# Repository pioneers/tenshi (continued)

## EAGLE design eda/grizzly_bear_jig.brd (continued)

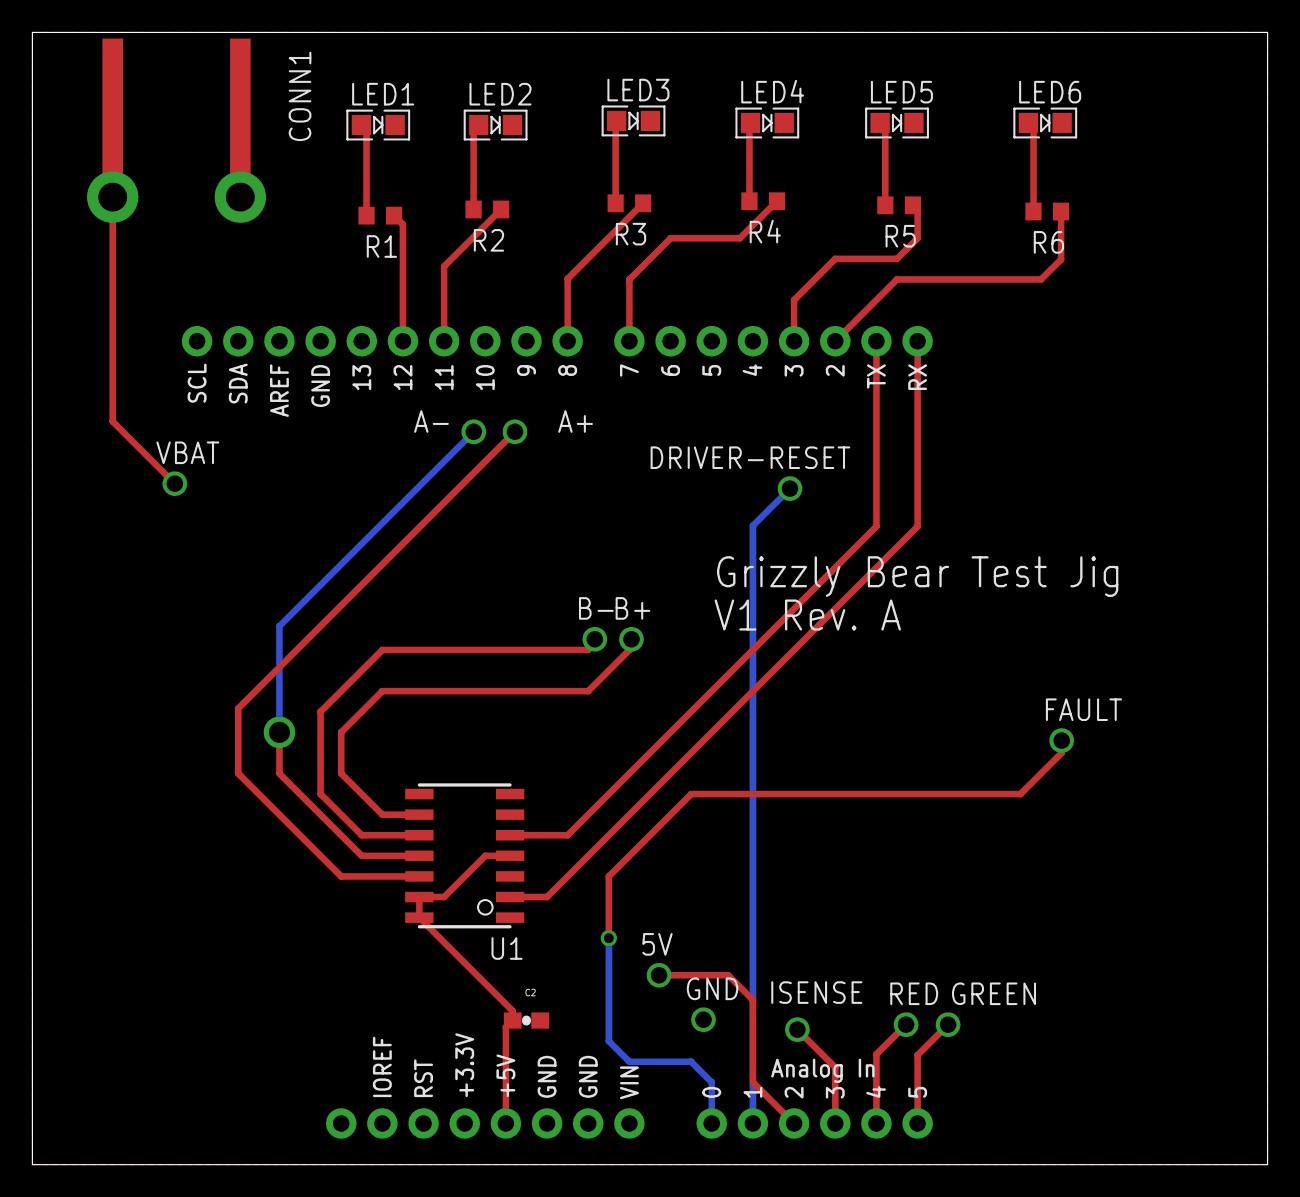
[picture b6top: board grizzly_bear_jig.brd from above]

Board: 2 copper layers, 76.2 x 69.8 mm, 28 parts (0 on the bottom side), 27 nets.

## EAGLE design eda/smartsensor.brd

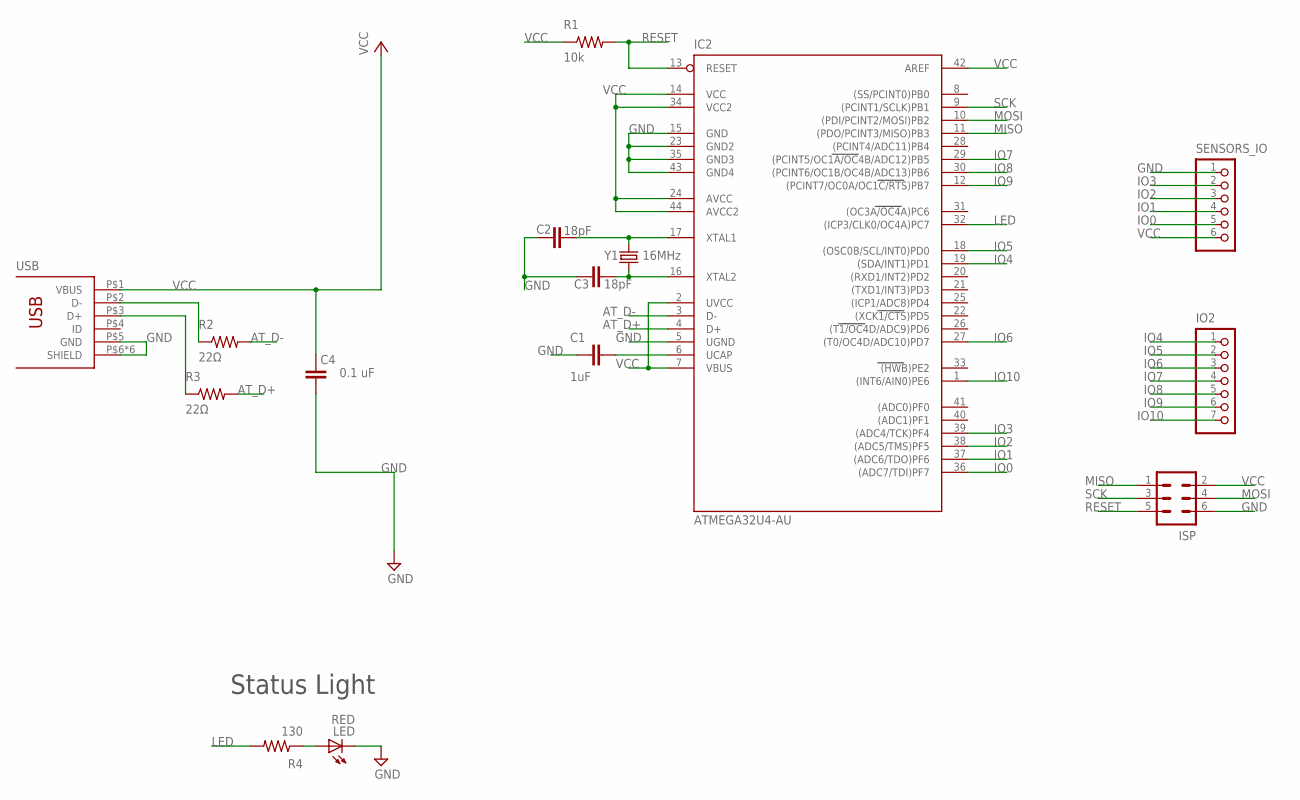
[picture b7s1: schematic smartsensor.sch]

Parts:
C1: 1uF; 0603-CAP
C2, C3: 18pF; 0603-CAP
C4: 0.1 uF; 0603-CAP
IC2: ATMEGA32U4-AU; TQFP44
IO2: PINHD-1X7; 1X07
ISP: MA03-2
LED: RED; LED-0805
R1: 10k; R0603
R2, R3: 22Ω; R0603
R4: 130; R0603
SENSORS_IO: PINHD-1X6STRAIN-RELIEF; 1X06-STRAINRELIEF
USB: USB-OTGMICRO-AB; USB-MICRO-AB
Y1: 16MHz; CRYSTAL-SMD-5.0X3.2-2PIN

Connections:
AT_D+: IC2.4 (D+), R3.2
AT_D-: IC2.3 (D-), R2.2
GND: C1.1, C2.1, C3.1, C4.1, IC2.5 (UGND), IC2.15 (GND), IC2.23 (GND2), IC2.35 (GND3), IC2.43 (GND4), ISP.6, LED.C, SENSORS_IO.1, USB.P$5 (GND), USB.P$6 (SHIELD), USB.P$7 (SHIELD), USB.P$8 (SHIELD), USB.P$9 (SHIELD), USB.P$10 (SHIELD), USB.P$11 (SHIELD)
IO0: IC2.36 ((ADC7/TDI)PF7), SENSORS_IO.5
IO1: IC2.37 ((ADC6/TDO)PF6), SENSORS_IO.4
IO2: IC2.38 ((ADC5/TMS)PF5), SENSORS_IO.3
IO3: IC2.39 ((ADC4/TCK)PF4), SENSORS_IO.2
IO4: IC2.19 ((SDA/INT1)PD1), IO2.1
IO5: IC2.18 ((OSC0B/SCL/INT0)PD0), IO2.2
IO6: IC2.27 ((T0/OC4D/ADC10)PD7), IO2.3
IO7: IC2.29 ((PCINT5/OC1A/OC4B/ADC12)PB5), IO2.4
IO8: IC2.30 ((PCINT6/OC1B/OC4B/ADC13)PB6), IO2.5
IO9: IC2.12 ((PCINT7/OC0A/OC1C/RTS)PB7), IO2.6
IO10: IC2.1 ((INT6/AIN0)PE6), IO2.7
LED: IC2.32 ((ICP3/CLK0/OC4A)PC7), R4.2
MISO: IC2.11 ((PDO/PCINT3/MISO)PB3), ISP.1
MOSI: IC2.10 ((PDI/PCINT2/MOSI)PB2), ISP.4
unnamed: C1.2, IC2.6 (UCAP)
unnamed: R3.1, USB.P$3 (D+)
unnamed: R2.1, USB.P$2 (D-)
unnamed: C2.2, IC2.17 (XTAL1), Y1.P$2 (2)
unnamed: C3.2, IC2.16 (XTAL2), Y1.P$1 (1)
unnamed: LED.A, R4.1
RESET: IC2.13 (RESET), ISP.5, R1.2
SCK: IC2.9 ((PCINT1/SCLK)PB1), ISP.3
VCC: C4.2, IC2.2 (UVCC), IC2.7 (VBUS), IC2.14 (VCC), IC2.24 (AVCC), IC2.34 (VCC2), IC2.42 (AREF), IC2.44 (AVCC2), ISP.2, R1.1, SENSORS_IO.6, USB.P$1 (VBUS)

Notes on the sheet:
Status Light

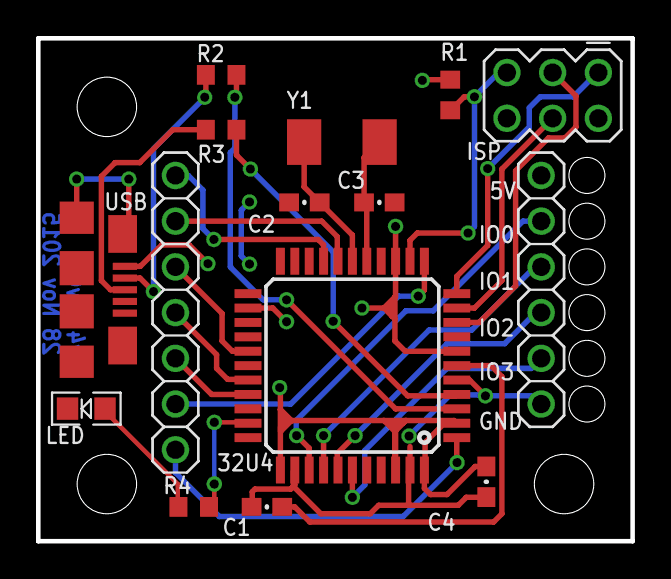
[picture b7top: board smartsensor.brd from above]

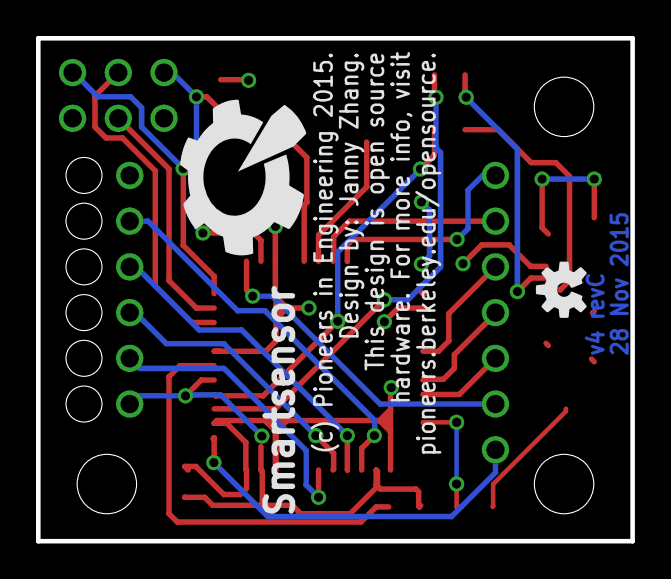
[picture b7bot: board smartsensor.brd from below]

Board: 2 copper layers, 33.0 x 27.9 mm, 20 parts (2 on the bottom side), 26 nets.

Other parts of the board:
HOLE1, HOLE2, HOLE3: STAND-OFF
U$1: PIE-LOGO-SMALL
U$2: OSHW-LOGO-S

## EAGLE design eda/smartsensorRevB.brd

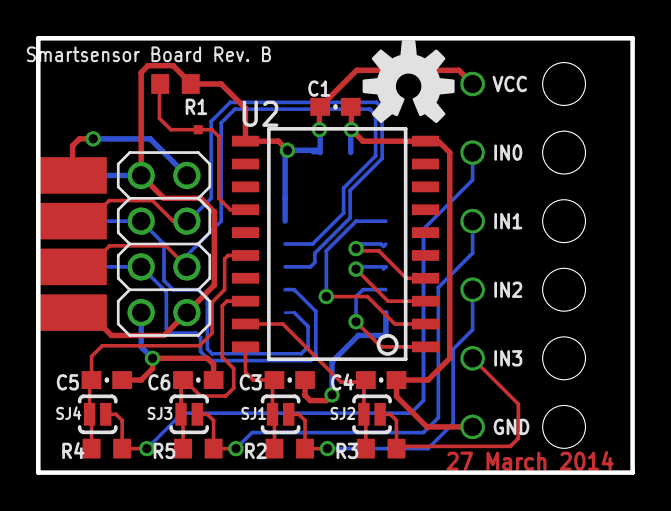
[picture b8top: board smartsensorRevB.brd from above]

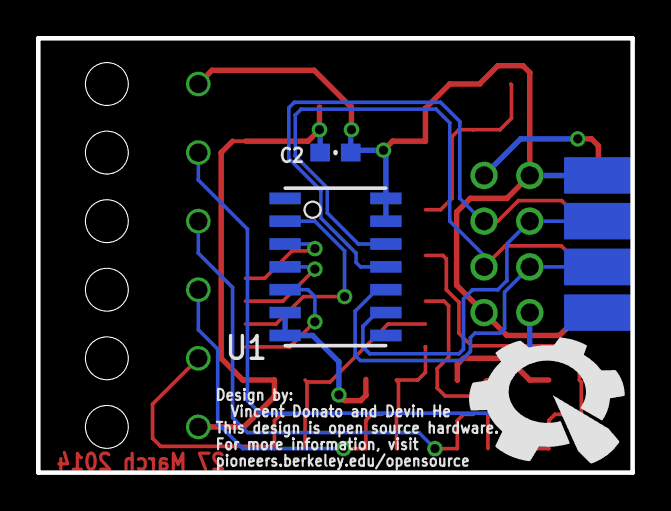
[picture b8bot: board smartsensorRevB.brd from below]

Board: 2 copper layers, 33.0 x 24.1 mm, 28 parts (3 on the bottom side), 19 nets.

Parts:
C1, C2: 0.1 uF; 0603-CAP
C3, C4, C5, C6: 0603-CAP
GND: WIRE_WITH_HOLE
IN0, IN1, IN2, IN3: WIRE_WITH_HOLE
R1: 10k; R0603
R2, R3, R4, R5: R0603
SJ1, SJ2, SJ3, SJ4: SOLDERJUMPERNO; SJ_2S-NO
TP1: TEST-POINT2; PAD.02X.02
U1: ISL83491SOIC; SOIC14
U2: ATTINY1634; SOIC20S
U$1: PIE-LOGO-SMALL
U$7: SENSOR_CONPTH; 2X4
U$8: SENSOR_CONSMD-EDGE; 2X4-EDGE
U$10: OSHW-LOGO-M
VCC: WIRE_WITH_HOLE

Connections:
5V: C1.1, C2.1, R1.2, U1.13, U1.14, U2.11, U$7.1, U$7.8, U$8.1, U$8.8, VCC.P$1
!RXE: U1.3, U2.4
A_N: U1.11, U$7.5, U$8.5
A_P: U1.12, U$7.3, U$8.3
B_N: U1.10, U$7.4, U$8.4
B_P: U1.9, U$7.6, U$8.6
CONN1: IN2.P$1, R2.1, SJ1.1
CONN2: IN3.P$1, R3.1, SJ2.1
CONN3: IN0.P$1, R4.1, SJ4.1
CONN4: IN1.P$1, R5.1, SJ3.1
GND: C1.2, C2.2, C3.1, C4.2, C5.2, C6.2, GND.P$1, U1.6, U1.7, U2.10, U$7.2, U$7.7, U$8.2, U$8.7
IO1: C3.2, R2.2, SJ1.2, U2.20
IO2: C4.1, R3.2, SJ2.2, U2.19
IO3: C5.1, R4.2, SJ4.2, U2.16
IO4: C6.1, R5.2, SJ3.2, U2.18
RESET: R1.1, TP1.P$1, U2.14
RX: U1.2, U2.2
TX: U1.5, U2.1
TXE: U1.4, U2.3
